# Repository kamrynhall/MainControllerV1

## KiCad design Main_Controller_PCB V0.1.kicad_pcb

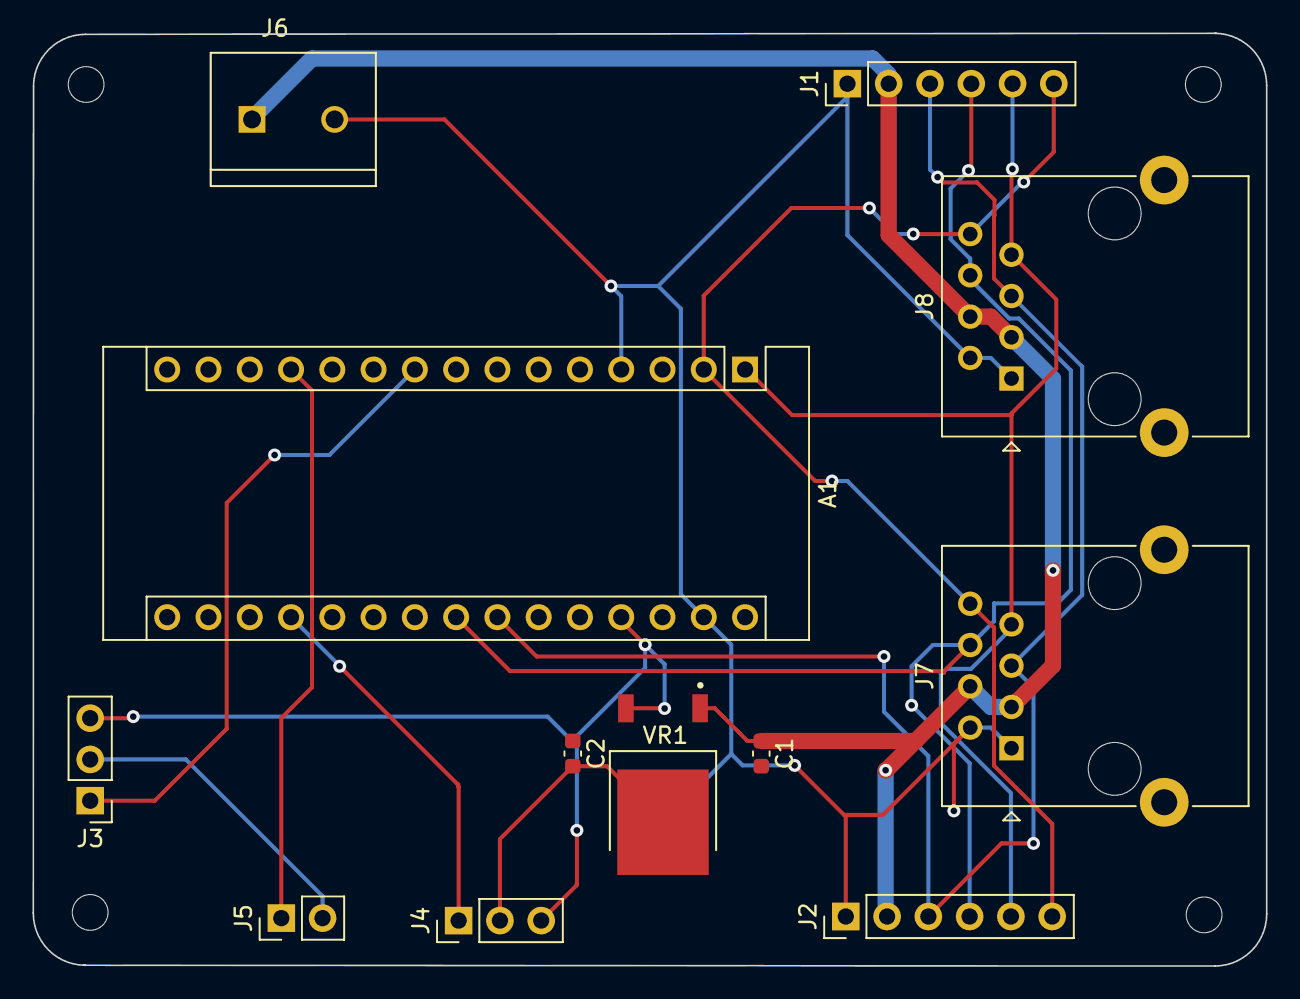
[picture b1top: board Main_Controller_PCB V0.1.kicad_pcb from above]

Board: 2 copper layers, 75.9 x 57.4 mm, 16 parts (0 on the bottom side), 10 nets.

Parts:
A1: Arduino_Nano_v3.x; Arduino_Nano
C1: 0.33 uF; C_0603_1608Metric
C2: 0.1uF; C_0603_1608Metric
H1, H2, H3, H4: MountingHole; MountingHole_2.2mm_M2
J1, J2: Pwr/Coms; PinHeader_1x06_P2.54mm_Vertical
J3: LED; PinHeader_1x03_P2.54mm_Vertical
J4: Foot Pedal; PinHeader_1x03_P2.54mm_Vertical
J5: Pedal PWM; PinHeader_1x02_P2.54mm_Vertical
J6: Screw_Terminal_01x02; TE_282837-2
J7, J8: 8P8C; RJ45_Ninigi_GE
VR1: LM78M05CDTX_NOPB; TO228P991X255-3N

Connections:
+5V: A1.27 (+5V), C2.1, J3.3, J4.3, VR1.3 (OUTPUT)
+12V: C1.1, J1.2, J2.2, J6.1, J7.3, J7.4, J8.3, J8.4, VR1.1 (INPUT)
/LED: A1.9 (D6), J3.1
/RXD: A1.1 (D1/TX), J1.5, J2.5, J7.7, J8.7
/SCL: A1.24 (A5), J1.3, J2.3, J7.5, J8.5
/SDA: A1.23 (A4), J1.4, J2.4, J7.6, J8.6
/TXD: A1.2 (D0/RX), J1.6, J2.6, J7.8, J8.8
/pedal: A1.19 (A0), J4.1
/pedal_pwm: A1.12 (D9), J5.1
GND: A1.4 (GND), A1.29 (GND), C1.2, C2.2, J1.1, J2.1, J3.2, J4.2, J5.2, J6.2, J7.1, J7.2, J8.1, J8.2, VR1.4 (GND)

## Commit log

2022-09-12 Routed PCB
